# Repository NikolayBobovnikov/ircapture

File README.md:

# ircapture
Infrared transmitter and receiver based on cheap STM32 board and of the shelf components

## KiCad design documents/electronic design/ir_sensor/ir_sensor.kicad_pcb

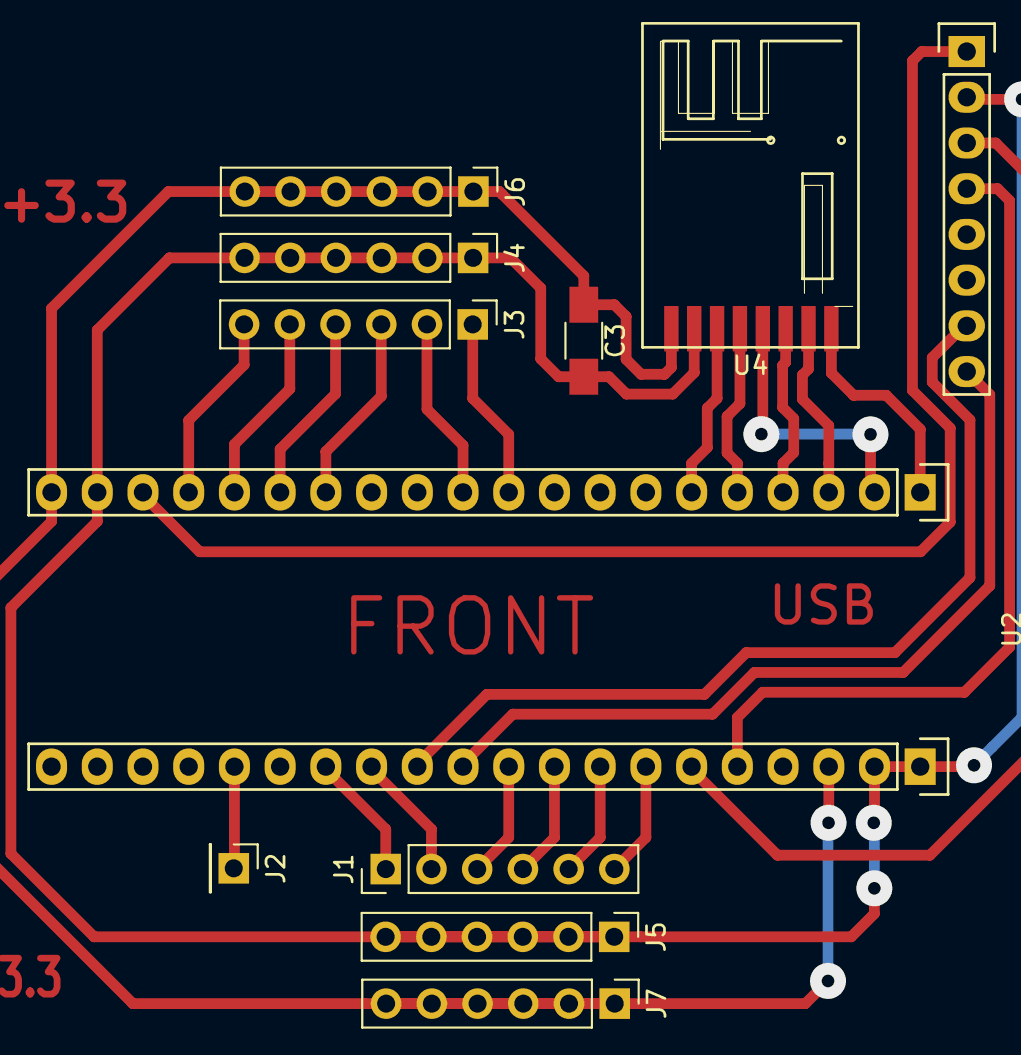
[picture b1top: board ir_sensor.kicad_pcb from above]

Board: 2 copper layers, 11 parts (0 on the bottom side), 26 nets.

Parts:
C3: 100uf; C_1206_HandSoldering
J1, J3, J4, J5, J6, J7: Conn_01x06; Pin_Header_Straight_1x06_Pitch2.54mm
J2: Conn_01x01; Pin_Header_Straight_1x01_Pitch2.54mm
U2: STM32F103HEADER; STM32F103_header_footprint
U3: MPU6050_module; MPU6050_pin_header_straight
U4: SE8R01_module; SE8R01_SMD

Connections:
+3V3: C3.1, J6.1, J6.2, J6.3, J6.4, J6.5, J6.6, J7.1, J7.2, J7.3, J7.4, J7.5, J7.6, U2.20, U4.1
+5V: U2.18, U3.1
AD0: U2.32, U3.7
GND: C3.2, J4.1, J4.2, J4.3, J4.4, J4.5, J4.6, J5.1, J5.2, J5.3, J5.4, J5.5, J5.6, U2.19, U3.2, U4.2
I2C_SCL: U2.26, U3.3
I2C_SDA: U2.25, U3.4
LED_DBG: J2.1, U2.36
MPU5060_INT: U2.31, U3.8
SE8R01_CE: U2.6, U4.3
SE8R01_CSN: U2.5, U4.4
SE8R01_IRQ: U2.1, U4.8
SPI_MISO: U2.3, U4.7
SPI_MOSI: U2.4, U4.6
SPI_SCK: U2.2, U4.5
input_1: J1.1, U2.34
input_2: J1.2, U2.33
input_3: J1.3, U2.30
input_4: J1.4, U2.29
input_5: J1.5, U2.28
input_6: J1.6, U2.27
input_7: J3.3, U2.14
input_8: J3.4, U2.15
input_9: J3.5, U2.16
input_10: J3.6, U2.17
input_11: J3.2, U2.11
input_12: J3.1, U2.10

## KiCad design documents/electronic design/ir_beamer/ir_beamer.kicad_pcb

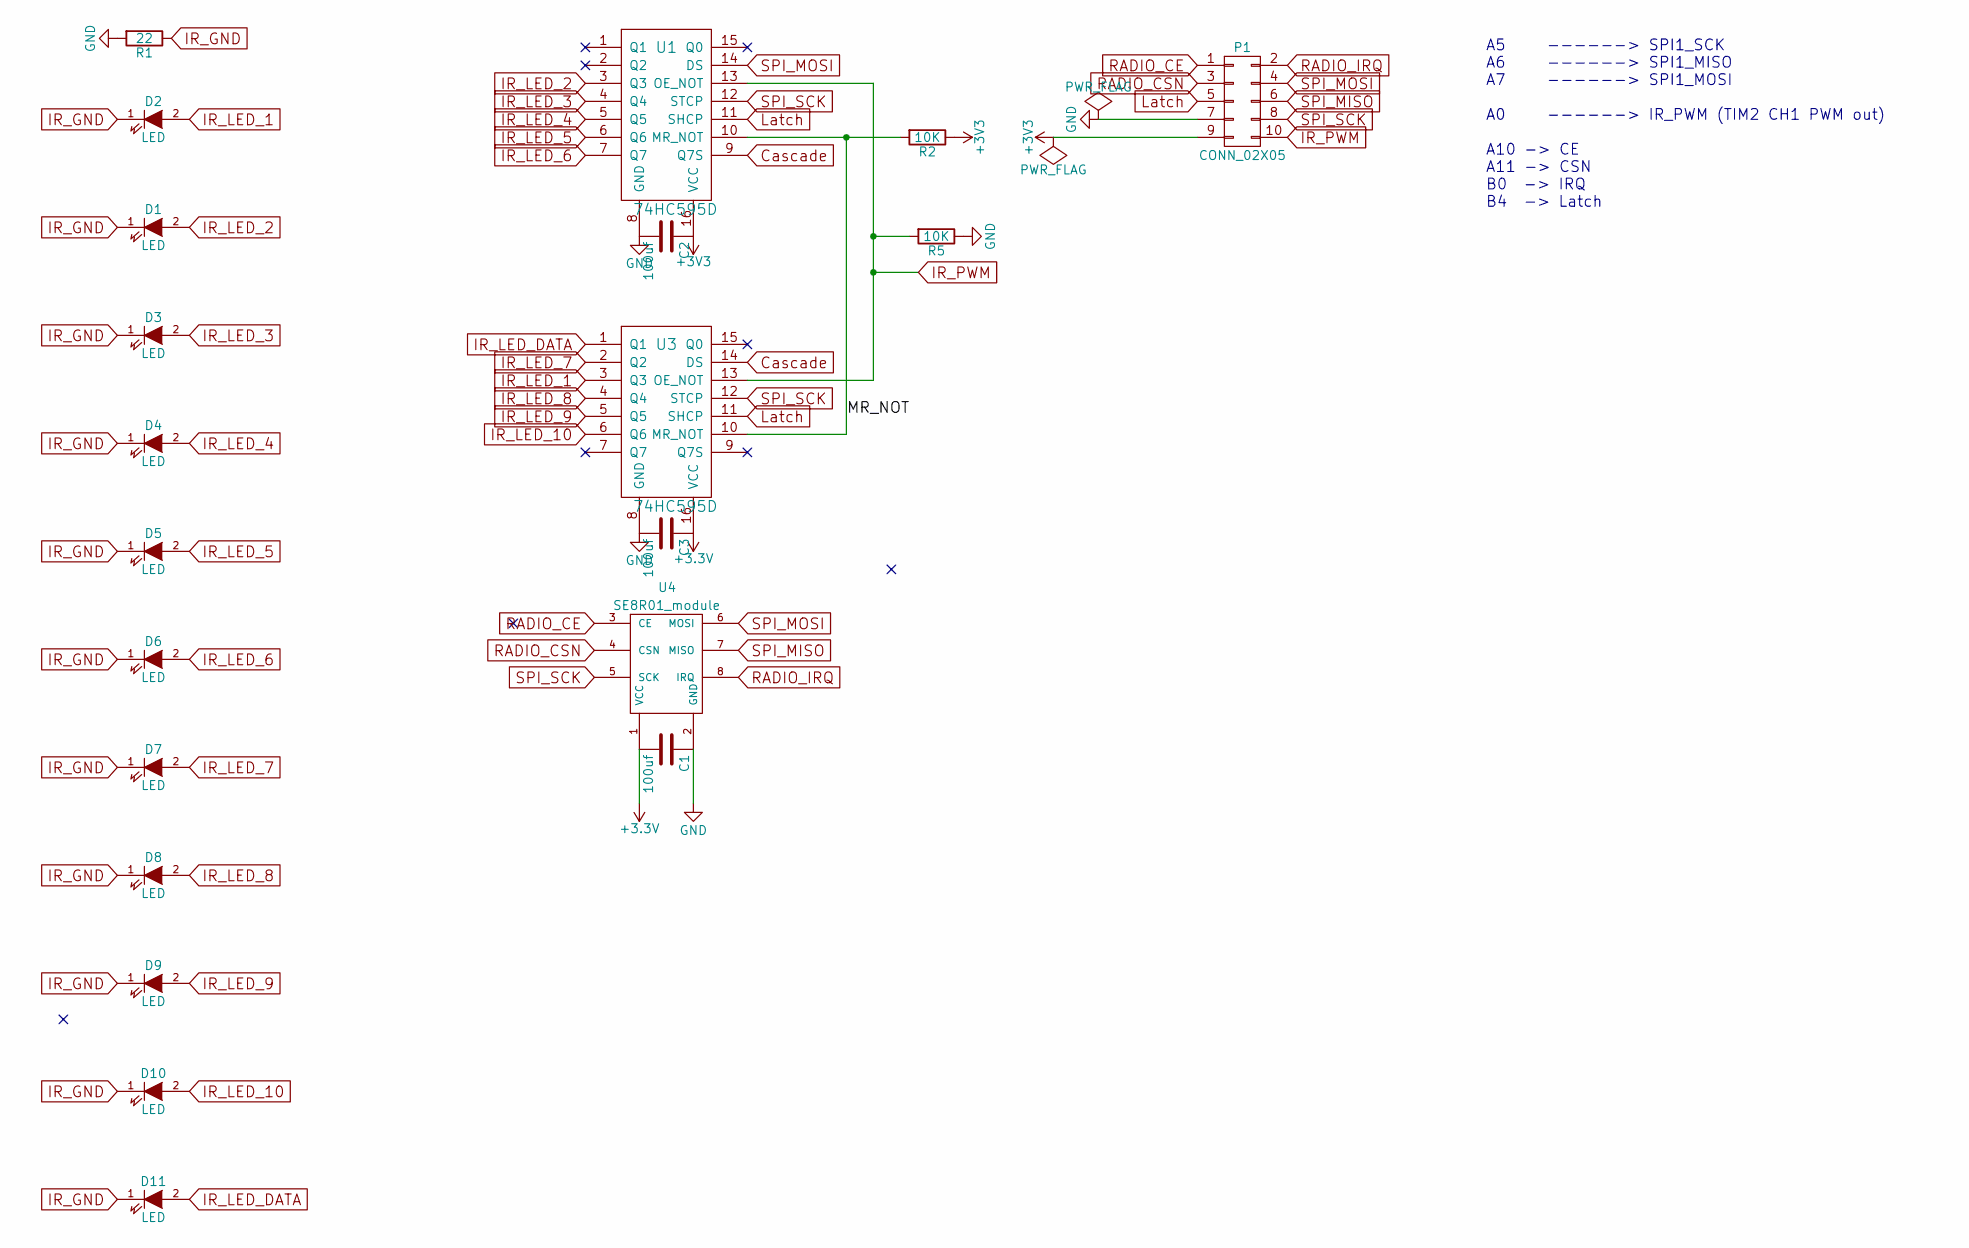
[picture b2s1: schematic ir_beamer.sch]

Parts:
C1: 100uf; C_0603_HandSoldering
C2, C3: 100uf; C_1206_HandSoldering
D1, D2, D3, D4, D5, D6, D7, D8, D9, D10, D11: LED; LED-5MM
P1: CONN_02X05; Pin_Header_Straight_2x05
R1: 22; C_0805_HandSoldering
R2, R5: 10K; C_0805_HandSoldering
U1, U3: 74HC595D; 74HC595D_SO16
U4: SE8R01_module; SE8R01

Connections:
/MR_NOT: R2.2, U1.10 (MR_NOT), U3.10 (MR_NOT)
Cascade: U1.9 (Q7S), U3.14 (DS)
GND: C1.1, C2.2, C3.2, P1.7, R1.2, R5.1, U1.8 (GND), U3.8 (GND), U4.2 (GND)
IR_GND: D1.1 (K), D2.1 (K), D3.1 (K), D4.1 (K), D5.1 (K), D6.1 (K), D7.1 (K), D8.1 (K), D9.1 (K), D10.1 (K), D11.1 (K), R1.1
IR_LED_1: D2.2 (A), U3.3 (Q3)
IR_LED_2: D1.2 (A), U1.3 (Q3)
IR_LED_3: D3.2 (A), U1.4 (Q4)
IR_LED_4: D4.2 (A), U1.5 (Q5)
IR_LED_5: D5.2 (A), U1.6 (Q6)
IR_LED_6: D6.2 (A), U1.7 (Q7)
IR_LED_7: D7.2 (A), U3.2 (Q2)
IR_LED_8: D8.2 (A), U3.4 (Q4)
IR_LED_9: D9.2 (A), U3.5 (Q5)
IR_LED_10: D10.2 (A), U3.6 (Q6)
IR_LED_DATA: D11.2 (A), U3.1 (Q1)
IR_PWM: P1.10, R5.2, U1.13 (OE_NOT), U3.13 (OE_NOT)
Latch: P1.5, U1.11 (SHCP), U3.11 (SHCP)
RADIO_CE: P1.1, U4.3 (CE)
RADIO_CSN: P1.3, U4.4 (CSN)
RADIO_IRQ: P1.2, U4.8 (IRQ)
SPI_MISO: P1.6, U4.7 (MISO)
SPI_MOSI: P1.4, U1.14 (DS), U4.6 (MOSI)
SPI_SCK: P1.8, U1.12 (STCP), U3.12 (STCP), U4.5 (SCK)

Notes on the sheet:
A5 ------> SPI1_SCK A6 ------> SPI1_MISO A7 ------> SPI1_MOSI A0 ------> IR_PWM (TIM2 CH1 PWM out) A10 -> CE A11 -> CSN B0 -> IRQ B4 -> Latch

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
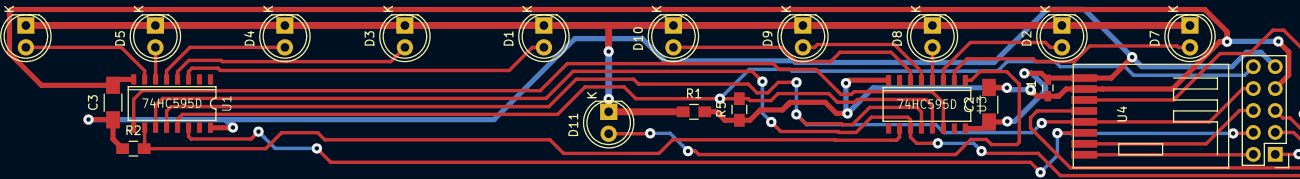
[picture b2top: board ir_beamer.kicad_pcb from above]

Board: 2 copper layers, 21 parts (0 on the bottom side), 24 nets.

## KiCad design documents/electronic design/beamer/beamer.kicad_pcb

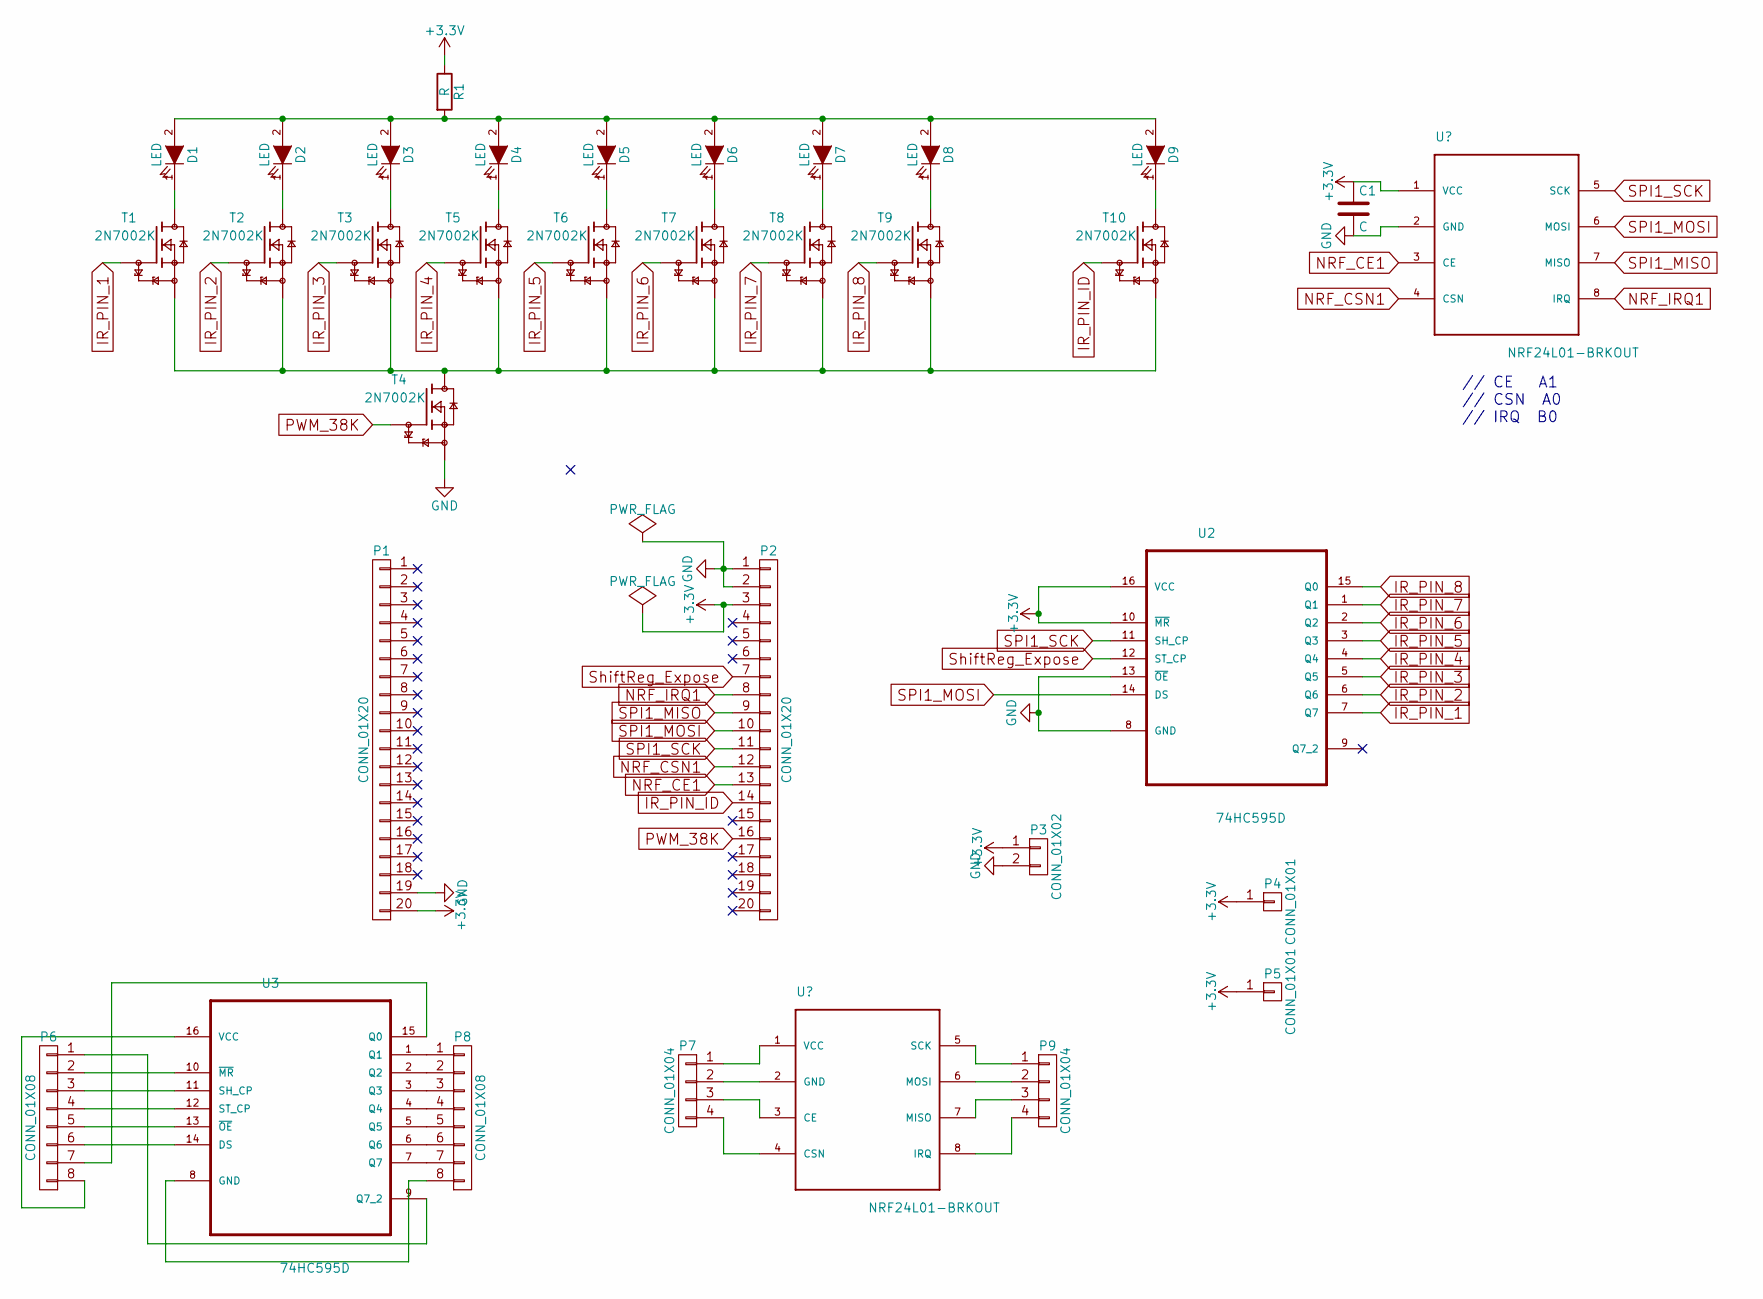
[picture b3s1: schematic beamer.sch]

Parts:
C1: C
D1, D2, D3, D4, D5, D6, D7, D8, D9: LED; LED-5MM
P1, P2: CONN_01X20; Socket_Strip_Straight_1x20
P3: CONN_01X02; Pin_Header_Straight_1x02
P4, P5: CONN_01X01; Pin_Header_Straight_1x01
P6, P8: CONN_01X08; Pin_Header_Straight_1x08
P7, P9: CONN_01X04; Pin_Header_Straight_1x04
R1: R; R_0805_HandSoldering
T1, T2, T3, T4, T5, T6, T7, T8, T9, T10: 2N7002K; SOT23
U2, U3: 74HC595D; SO16

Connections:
+3V3: C1.1, P1.20, P2.3, P3.1, P4.1, P5.1, R1.1, U2.10 (~MR), U2.16 (VCC); also elsewhere on the board
GND: C1.2, P1.19, P2.1, P2.2, P3.2, T4.2 (S), U2.8 (GND), U2.13 (~OE); also elsewhere on the board
IR_PIN_1: T1.1 (G), U2.7 (Q7)
IR_PIN_2: T2.1 (G), U2.6 (Q6)
IR_PIN_3: T3.1 (G), U2.5 (Q5)
IR_PIN_4: T5.1 (G), U2.4 (Q4)
IR_PIN_5: T6.1 (G), U2.3 (Q3)
IR_PIN_6: T7.1 (G), U2.2 (Q2)
IR_PIN_7: T8.1 (G), U2.1 (Q1)
IR_PIN_8: T9.1 (G), U2.15 (Q0)
IR_PIN_ID: P2.14, T10.1 (G)
NRF_CE1: P2.13; also elsewhere on the board
NRF_CSN1: P2.12; also elsewhere on the board
NRF_IRQ1: P2.8; also elsewhere on the board
unnamed: D1.1 (K), T1.3 (D)
unnamed: D1.2 (A), D2.2 (A), D3.2 (A), D4.2 (A), D5.2 (A), D6.2 (A), D7.2 (A), D8.2 (A), D9.2 (A), R1.2
unnamed: D2.1 (K), T2.3 (D)
unnamed: D3.1 (K), T3.3 (D)
unnamed: D4.1 (K), T5.3 (D)
unnamed: D5.1 (K), T6.3 (D)
unnamed: D6.1 (K), T7.3 (D)
unnamed: D7.1 (K), T8.3 (D)
unnamed: D8.1 (K), T9.3 (D)
unnamed: D9.1 (K), T10.3 (D)
unnamed: P6.1, U3.9 (Q7_2)
unnamed: P6.2, U3.10 (~MR)
unnamed: P6.3, U3.11 (SH_CP)
unnamed: P6.4, U3.12 (ST_CP)
unnamed: P6.5, U3.13 (~OE)
unnamed: P6.6, U3.14 (DS)
unnamed: P6.7, U3.15 (Q0)
unnamed: P6.8, U3.16 (VCC)
unnamed 58: P7.1; also elsewhere on the board
unnamed 59: P7.2; also elsewhere on the board
unnamed 60: P7.3; also elsewhere on the board
unnamed 61: P7.4; also elsewhere on the board
unnamed: P8.1, U3.1 (Q1)
unnamed: P8.2, U3.2 (Q2)
unnamed: P8.3, U3.3 (Q3)
unnamed: P8.4, U3.4 (Q4)
unnamed: P8.5, U3.5 (Q5)
unnamed: P8.6, U3.6 (Q6)
unnamed: P8.7, U3.7 (Q7)
unnamed: P8.8, U3.8 (GND)
unnamed 70: P9.1; also elsewhere on the board
unnamed 71: P9.2; also elsewhere on the board
unnamed 72: P9.3; also elsewhere on the board
unnamed 73: P9.4; also elsewhere on the board
unnamed: T1.2 (S), T2.2 (S), T3.2 (S), T4.3 (D), T5.2 (S), T6.2 (S), T7.2 (S), T8.2 (S), T9.2 (S), T10.2 (S)
PWM_38K: P2.16, T4.1 (G)
SPI1_MISO: P2.9; also elsewhere on the board
SPI1_MOSI: P2.10, U2.14 (DS); also elsewhere on the board
SPI1_SCK: P2.11, U2.11 (SH_CP); also elsewhere on the board
ShiftReg_Expose: P2.7, U2.12 (ST_CP)

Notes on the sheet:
// CE A1 // CSN A0 // IRQ B0

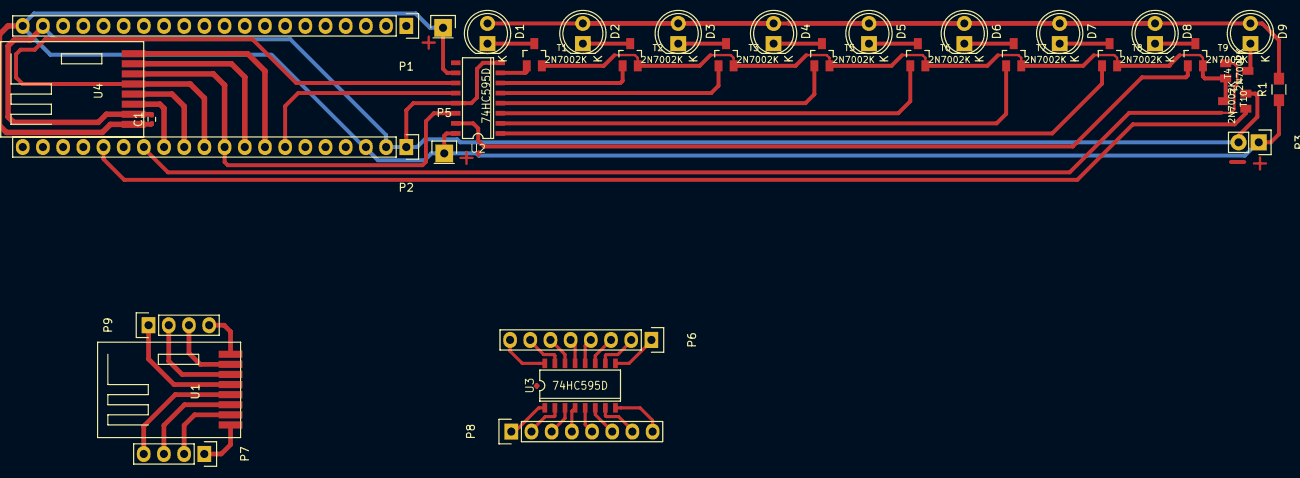
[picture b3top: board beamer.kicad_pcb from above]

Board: 2 copper layers, 34 parts (0 on the bottom side), 54 nets.

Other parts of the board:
U1, U4: NRF24L01-BRKOUT; se8r01_smd

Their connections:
+3V3: U4.1; also elsewhere on the board
GND: U4.2; also elsewhere on the board
NRF_CE1: U4.3; also elsewhere on the board
NRF_CSN1: U4.4; also elsewhere on the board
NRF_IRQ1: U4.8; also elsewhere on the board
unnamed 58: U1.1; also elsewhere on the board
unnamed 59: U1.2; also elsewhere on the board
unnamed 60: U1.3; also elsewhere on the board
unnamed 61: U1.4; also elsewhere on the board
unnamed 70: U1.5; also elsewhere on the board
unnamed 71: U1.6; also elsewhere on the board
unnamed 72: U1.7; also elsewhere on the board
unnamed 73: U1.8; also elsewhere on the board
SPI1_MISO: U4.7; also elsewhere on the board
SPI1_MOSI: U4.6; also elsewhere on the board
SPI1_SCK: U4.5; also elsewhere on the board

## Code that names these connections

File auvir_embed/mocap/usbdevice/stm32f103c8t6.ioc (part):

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Mcu.Name=STM32F103C(8-B)Tx
Mcu.Package=LQFP48
Mcu.UserName=STM32F103C8Tx
PA0-WKUP.GPIOParameters=GPIO_Label
PA0-WKUP.GPIO_Label=NRF24_CSN1
PA0-WKUP.Signal=GPIO_Output
PA1.GPIOParameters=GPIO_Label
PA1.GPIO_Label=NRF24_CE1
PA1.Signal=GPIO_Output
PA11.Mode=Device
PA11.Signal=USB_DM
PA12.Mode=Device
PA12.Signal=USB_DP
PA13.Mode=Serial_Wire
PA13.Signal=SYS_JTMS-SWDIO
PA14.Mode=Serial_Wire
PA14.Signal=SYS_JTCK-SWCLK
PA2.GPIOParameters=GPIO_Label
PA2.GPIO_Label=NRF24_CSN2
PA2.Signal=GPIO_Output
PA3.GPIOParameters=GPIO_Label
PA3.GPIO_Label=NRF24_CE2
PA3.Signal=GPIO_Output
PA5.Mode=Full_Duplex_Master
PA5.Signal=SPI1_SCK
PA6.Mode=Full_Duplex_Master
PA6.Signal=SPI1_MISO
PA7.Mode=Full_Duplex_Master
PA7.Signal=SPI1_MOSI
PB0.GPIOParameters=GPIO_Label,GPIO_PuPd
PB0.GPIO_Label=NRF24_IRQ1
PB0.GPIO_PuPd=GPIO_PULLUP
PB0.Signal=GPIO_Input
PB1.GPIOParameters=GPIO_Label,GPIO_PuPd
PB1.GPIO_Label=NRF24_IRQ2
PB1.GPIO_PuPd=GPIO_PULLUP
PB1.Signal=GPIO_Input
PB3.GPIOParameters=GPIO_Label,GPIO_Speed
PB3.GPIO_Label=LED_DBG
PB3.GPIO_Speed=GPIO_SPEED_FREQ_HIGH
PB3.Signal=GPIO_Output
PC13-TAMPER-RTC.GPIOParameters=GPIO_Label,GPIO_Speed
PC13-TAMPER-RTC.GPIO_Label=LED_ONBOARD
PC13-TAMPER-RTC.GPIO_Speed=GPIO_SPEED_FREQ_LOW
PC13-TAMPER-RTC.Signal=GPIO_Output
PD0-OSC_IN.Mode=HSE-External-Oscillator
PD0-OSC_IN.Signal=RCC_OSC_IN
PD1-OSC_OUT.Mode=HSE-External-Oscillator
PD1-OSC_OUT.Signal=RCC_OSC_OUT
RCC.SYSCLKFreq_VALUE=72000000
RCC.SYSCLKSource=RCC_SYSCLKSOURCE_PLLCLK
board=stm32f103c8t6

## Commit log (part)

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2016-01-01 Works in a dirty way: turned off some timing checks. Data is being received correctly. All states are passed (start bits, data, stop bits)
2016-01-02 simplifid debugging toggling; fixed bug in last data bit reading which lead to missing each nd of data frame; added (previously turned off) check in stop bit sequence check
2016-01-02 fix 38K carrier frequency in transmitter timer settings
2016-01-03 added parameter for direct/indirect logic to handle reversed signal from IR receiver. Debugging
2016-01-03 minor update
2016-01-04 added "static" specifier for private(used in the receiver module only) functions
2016-01-05 cleanup, refactorig
2016-01-06 update setup environment script, ignore *~ files in git
2016-01-06 update setup env script
2016-01-09 changed debugging scripts for use with stlink v2 programmer
2016-01-10 adjust timings for transmitter (to work with TL1838 ir receiver)
2016-01-10 adjust timings for transmitter to increase throughput
2016-01-11 added indirect logic to transmitter
2016-01-11 fixing receiver for indirect logic. Decoding signal directly from transmitter works
2016-01-12 remove off-on switches during data transmittion; update debugging pulses
2016-01-12 more deep refactoring, add comment describing packet structure
2016-01-12 fix receiving from TL1838 by adjusting delay check timings
2016-01-13 add routine prototype and comment with pseudocode - for all sensors to send data without interferring with each other
2016-01-13 add verifiation of received data. A lot of FP receivings
2016-01-14 fix typo, updated ignore files, update coocox proj
2016-01-16 add installing wine to setup environment script
2016-01-16 add [TODO: install unreal engine] to setup environment
2016-01-16 move DEBUG define to infrared.c
2016-01-16 refactoring for debugging in transmitter
2016-01-16 add receiving test data from UART to be transmitted to IR
2016-01-17 update UART for transmitter
2016-01-17 regenerate init code with cubemx for receiver; add USART
2016-01-18 added sending received data to uart in receiver, needs tesing
2016-01-19 fix compiler warning: move static function declarations to infrared.c
2016-01-19 fix compiler warnings in receiver (partially)
2016-01-19 use tim_init() routines from dev branch (depending on whether logic is direct or not)
2016-01-19 fixed bug in tim4 initialization: use tim_ic_init instead of tim_base_init. Bug in cubemx?
2016-01-19 restructure protocol for receiver. TODO: debug
2016-01-19 update protocol timings in transmitter
2016-01-20 refactoring
2016-01-20 reviewed routines for receiver; revactoring
2016-01-20 fixes+revactoring
2016-01-20 done udpating transmitter routines; in progress: updating receiver
2016-01-20 found issue, need to fix
2016-01-21 refactored debugging scaffoldings. Use inline functions instead of preprocessor
2016-01-21 cleanup unused code for debugging
2016-01-21 fix in receiver; now reading works, though unreliably
2016-01-21 refactoring; added debugging functions
2016-01-22 fixing receiver is done, data is being received and its correctness verified
2016-01-22 updated cubemx proejct (added CRC, SPI2, remove I2C), regenerated init code
2016-01-22 rm redundant files
2016-01-22 add separate routine for init gpio for debugging
2016-01-22 fix merge conflict
2016-01-22 update protocol - decreased length of bits and delays
2016-01-22 remove redundant coocox project files
2016-01-22 get back stuff for UART
2016-01-24 add simple test of transmitter using UART. TODO: proper design of desktop app
2016-01-24 sending received data moved to receiver
2016-01-24 add UART interrupt; regenerate init code cubemx
2016-01-24 use non blocking receiving of UART data in transmitter
2016-01-25 add stubs for sensor/beamer hub routines
2016-01-28 added routine for sending data by sensors. WIP
2016-01-30 add draft for beamer electronic schematic
2016-01-31 update on sensor registration routines
2016-02-04 add init for gpio debug pins, add declarations for handlers
2016-02-04 Add multichannel output to transmitter. WIP
2016-02-05 fix bug in init gpio routine for transmitter
2016-02-05 implemented switching gpio pins for multichannel beamer
2016-02-07 fix for separate transmitter channels; adjust time shifts for bit and delay lengths
2016-02-09 add project for sensor-hid
2016-02-11 remove UART, add SPI
2016-02-17 regenerate USB project for CDC
2016-02-17 update CDC
2016-02-20 add to receiver led indication of received/verified angle
2016-02-21 minor refactoring for LED receiver indicator
2016-02-21 update for nrf24l01
2016-02-21 refactor
2016-02-22 update SPI interfacing with radiomodule. Read/Write to registers seems to work
2016-02-23 minor updates for nrf24
2016-02-23 save current state
2016-02-23 add reset nrf24
2016-02-23 updates for nrf24; refactoring
2016-02-26 make CE low after 15 us of transmitting
2016-02-27 save edits
2016-02-28 add lib for se8 chip
2016-02-28 use lib for se8 chip. Works!
2016-02-29 save
2016-02-29 add timer for us delaay
2016-03-01 update coocox project
2016-03-01 add interrupt for irq pin; not working yet
2016-03-02 revert for se8r01 add todo refactoring
2016-03-02 minor refactor
2016-03-02 fix init issue; add led for debugging
2016-03-03 fix timing after calibration
2016-03-04 update timings. Works better
2016-03-04 fix receiver routine. Helped a lot
2016-03-05 add power on/off functions; update timings
2016-03-05 save changes. need to fix us delay routine
2016-03-06 use base timer for delay
2016-03-06 update timings, seems to work OK now. WIP
2016-03-08 fix stuck on power-on issue in rf transmitter setup
2016-03-09 dont blink if paket is lost; flush tx buf instead of rx in transmitter routine
2016-03-12 increase IR protocol timings to make it more reliable; remove flashing TX buf if tx_status==SENDING
2016-03-13 remove tmp file
2016-03-13 make radio header and src files common among receiver, tranmitter and mocap device projects
2016-03-13 move common functions to common files; add SPI to mocap_device
2016-03-15 addtional LED indicator
2016-03-19 refactor rx (1)
2016-03-19 use common infrared.h
2016-03-19 use common infrared.c file
2016-03-19 move to project specific files. common stuff moved to common files
2016-03-20 use primitive delay
2016-03-20 fix direct/inverse logic for IR rx/tx
2016-03-20 separate LED for indicating radio and IR events
2016-03-20 fix GPIO setting for LED; regenerate using updated CubeMX library
2016-03-20 add I2C, remove UART
2016-03-20 remove redundant project
2016-03-24 setting up EXTI mode for GPIO
2016-03-24 added EXTI to GPIO
2016-03-27 regenerate receiver project
2016-03-27 adjust IRQ for for tx routine
2016-03-27 regenerate project for usbdevice
2016-03-28 add check for NULLin USB_Set_Tx_buf
2016-03-28 remove unused modules; regenerate in CubeMX, update coocox project
2016-03-30 bugfix
2016-03-30 add project for IAR
2016-03-31 refactoring, cleaning compiler messages
2016-03-31 generate project for gcc tools
2016-03-31 add python scrypt for input controller prototype
2016-03-31 minor update in the script
2016-04-01 fix unicode usb issue
2016-04-02 add pcb draft for smd radio shield
2016-04-02 add ready to pring shield pcb
2016-04-03 change IRQ pin for radio to simplify PCB
2016-04-03 add callback for radio rx in usbdevice and receiver
2016-04-04 fix interrupts for radio, now no need to call "stuff without interrupts dont work" in the loop
2016-04-04 work without interrupt, only first time
2016-04-04 work without interrupt, OK
2016-04-04 minor update GPIO IRQ setting
2016-04-04 add getstatus routine
2016-04-05 add salt to beginning of transmitted package (so it is different every time); fix rx issue (comment out flushing rx buffer) TODO: fix flushing
2016-04-05 fix radio for usbdevice
2016-04-06 Squashed commit of the following:
    commit 83f46a002bdff34af67eec3181483785b5ffac2d
    Author: Nikolay Bobovnikov <nbobovnikov@Nbobovnikov.home.softech.ru>
    Date: Wed Apr 6 17:05:55 2016 +0300
    update coocox project for usbdevice
    commit 8fd49c79095f334321a6e803f5335ebea198c43e
    Author: Nikolay Bobovnikov <nbobovnikov@Nbobovnikov.home.softech.ru>
2016-04-06 update workflow diagram for usbdevice
2016-04-07 update diagrams with workflow for usbdevice, beamers and sensors
2016-04-08 save workflow diagrams to jpeg
2016-04-10 Add support for separate radiomodules controlled by same SPI
2016-04-10 refactor, add usb device registration routine
2016-04-11 refactor getting/setting type of radiomessage
2016-04-11 consider contents of message data depending on its type; add registration procedure for beamers
2016-04-13 add processing of sensor data; add routine to update radiomodule settings (address, channel); update registration info structure (add data related to usbdevice)
2016-04-14 cleanup for transmitter; remove constant definitions from cubemx project. Need to test
2016-04-17 update schematics and pcb projects
2016-04-18 finish pcb for beamer (prototype v1)
2016-04-18 thick traces
2016-04-20 change pin numbers in transmitter routine; remake pcb
2016-04-20 add capacitor to pcb
2016-04-23 exclude from gitignore folder with documents
2016-04-23 remove lib
2016-04-23 add lib files for kicad
2016-04-24 bugfixes and refactoring from hackaton
2016-04-27 fix transmitter issue
2016-05-02 add defines to mxconstants.h
2016-05-10 fix IR issue in transmitter; minor updates
2016-05-13 add ssh to install env script
2016-06-05 fixing pin mapping for beamer; WIP
2016-06-06 add blink function for debugging
2016-06-19 updatebeamer schematic
2016-06-24 update PCB for beamer, fix pin assignment for radiomodule
2016-06-24 minor update in beamer pcb layout
2016-06-27 TODO: update STM32Cube project to use TIM2 CH1 for pwm generation instead of TIM4
2016-06-27 add comment for PWM generation pin
2016-07-13 add new libraries
2016-07-14 fix pin numbers in ir_beamer
2016-07-16 add test code for 74HC595D
2016-07-17 both shift register and radio module works simultaneously. Need to update transmitter logic - switch between IR channels
2016-07-17 update transmitter. Need to update switching IR channels (LEDs)
2016-07-18 move to shift register
2016-07-19 create new pcb project for ir receiver
2016-07-20 make double sided pcb for beamer
2016-07-21 update pcb for beamer (use 5V to drive LED)
2016-07-25 update PCB projects for beamer and sensor
2016-07-25 use c++ compiler
2016-07-27 minor update in beamer pcb (added vias for pwm_gnd signal)
2016-07-28 add test pcb beamer v0.1
2016-08-03 add ltspice simulation circuit
2016-08-10 fix beamer pcb
2016-08-11 increase thicknesse of routes and vias in beamer pcb
2016-08-21 update beamer settings for shift register according to updated pcb
2016-08-21 update beamere pcb - MR_TOT in shift register, pull down
2016-08-22 fix mistake with pull up/ and down resistors in beamer pcb
2016-11-16 add generation of dir local file for emacs
2016-12-03 refactor common part of CMakeLists project into separate file in /mocap
2016-12-15 adjusting transmitter project for development under windows with emacs
2016-12-17 fix cmake project files
2016-12-19 update bat script for running openocd
2017-03-06 fix declaration of SHCP pin in shift register. TODO: fix wiring in PCB
2017-03-14 change sending 16 bit values through SPI
2017-05-30 change generated files to new CubeMX
2017-05-30 add USB device
2017-05-31 move to c++
2017-06-01 sending ADC values over USB - wip
2017-06-01 minor fix usbdevice, update script for usb host
2017-06-04 add animated plot of ADC values
2017-06-11 add separate function for PWM lighting
2017-06-11 send array of 64 adc values
2017-06-13 experimenting with filters: WIP
2017-06-13 adjust filtering
2017-06-13 add zero crossing detection
2017-10-05 update PCB for IR receiver
2017-10-05 update PCB (submodule)
2017-10-17 update projects
2017-10-17 fix some issues with receiver project; WIP
2017-10-19 update file structure
2017-10-20 refactor code for radiomodule; WIP
2017-10-25 fix minor issue, make compile
2017-10-26 update setting compiler; change port for openocd
2017-10-27 adjust scripts for openocd/gdb
2017-10-29 remove pin defines for second radio module (put under ifdef)
2017-10-29 regenerate cubemx project; refactor auvir::htim_Delay; test c++ static objects
2017-10-30 fix compilation errors; wip - experimenting
2017-10-31 fix init for mpu6050
2017-11-01 add script for running openocd
2017-11-02 update pin mapping, regenerate for i2c2,spi2, number of tim input channels. WIP
2017-11-03 adjust pcb
